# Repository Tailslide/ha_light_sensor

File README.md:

# Home Assistant Mouse Trap Monitor

An ESP32-based mouse trap monitoring system that integrates with Home Assistant via MQTT. The system uses light-dependent resistors (LDRs) to detect both the trap state (triggered/ready) and battery status (ok/low), providing real-time updates to your Home Assistant instance.

## Features

- Monitors mouse trap state (triggered/ready) using an LDR sensor
- Monitors battery status (ok/low) using a second LDR sensor
- Optional external wake circuit support for immediate trap detection
- Integrates with Home Assistant via MQTT
- Power-efficient design with deep sleep between readings
- 24-hour heartbeat publishing to ensure device health monitoring
- MQTT will messages for accurate availability tracking
- Configurable sampling parameters and thresholds
- Automatic state persistence across deep sleep cycles
- Robust WiFi and MQTT connection handling
- Modular code structure for better maintainability
- Configurable debug output

## Project Structure

The project follows a modular architecture for better organization and maintainability:

```
├── main/                  # Core application code
│   ├── include/          # Header files
│   │   ├── common.h     # Common definitions and utilities
│   │   ├── wifi_manager.h # WiFi connection management
│   │   ├── mqtt_manager.h # MQTT client operations
│   │   ├── sensor_manager.h # ADC and sensor handling
│   │   ├── led_controller.h # LED control functions
│   │   └── diagnostic.h  # Diagnostic mode operations
│   ├── src/             # Source files
│   │   ├── main.c      # Main application entry
│   │   ├── wifi_manager.c # WiFi implementation
│   │   ├── mqtt_manager.c # MQTT implementation
│   │   ├── sensor_manager.c # Sensor implementation
│   │   ├── led_controller.c # LED implementation
│   │   └── diagnostic.c # Diagnostic implementation
│   └── CMakeLists.txt   # Component build configuration
└── traps/               # Trap-specific configurations
    ├── backdoor/       # Back door trap config
    │   ├── config.h.template # Configuration template
    │   └── secrets.h.template # Credentials template
    ├── garage_near/    # Garage near trap config
    │   ├── config.h.template # Configuration template
    │   └── secrets.h.template # Credentials template
    └── template/       # Template for new traps
        ├── config.h.template # Configuration template
        └── secrets.h.template # Credentials template
```
## Hardware Requirements

- ESP32 development board ( M5Stamp C3)
- 2x Light Dependent Resistors (LDRs)
- Voltage divider resistors for LDRs
- Mouse trap with status LED and optional battery status LED (I use the OWL electronic mouse trap)

### Optional Wake Circuit Components
- TLV7011 comparator (or similar)
- GL5539 LDR (recommended for best sensitivity)
- 10kΩ resistor for LDR voltage divider
- 10kΩ trim potentiometer for threshold adjustment
- Connecting wires

## Pin Configuration

- GPIO4: LDR sensor for trap state detection (not needed if using wake circuit)
- GPIO1: LDR sensor for battery status detection
- GPIO2: Built-in RGB LED (using ESP32's led_strip driver)
- GPIO5: Wake circuit input (when USE_WAKE_CIRCUIT=1)

### Wake Circuit Connections
If using the optional wake circuit:
1. TLV7011 Pin 1 (OUT) → ESP32 GPIO5
2. TLV7011 Pin 2 (VEE) → GND
3. TLV7011 Pin 3 (IN+) → LDR voltage divider midpoint
4. TLV7011 Pin 4 (IN-) → Trim pot wiper (middle pin)
5. TLV7011 Pin 5 (VDD) → 3.3V

LDR Circuit:
```
3.3V ----[LDR]----+----[10kΩ]---- GND
                  |
                  +---- TLV7011 Pin 3 (IN+)
```

Trim Pot Circuit:
```
3.3V ----[10kΩ Trim Pot]----+---- GND
                            |
                            +---- TLV7011 Pin 4 (IN-)
```
- GPIO2: Built-in RGB LED (using ESP32's led_strip driver)

## Software Requirements

- ESP-IDF v5.x
- Home Assistant with MQTT broker

## Setup Instructions

The project now supports multiple mouse traps with individual configurations. Each trap has its own configuration directory under `traps/`.

### Available Traps
- `backdoor` - Back door mouse trap (original)
- `garage_near` - Garage near entrance trap
- Additional traps can be added by copying the `template` directory

### Power Optimization Settings

The project includes a `sdkconfig.defaults` file with optimized settings for power consumption:

```
# Power Management - Enable automatic power saving
CONFIG_PM_ENABLE=y
CONFIG_PM_DFS_INIT_AUTO=y
CONFIG_PM_USE_RTC_TIMER_REF=y

# CPU Frequency - Lower to 80MHz to save power
CONFIG_ESP_DEFAULT_CPU_FREQ_MHZ_80=y
CONFIG_ESP_DEFAULT_CPU_FREQ_MHZ=80

# Flash Power Down in Deep Sleep
CONFIG_ESP_SLEEP_POWER_DOWN_FLASH=y

# WiFi Power Saving
CONFIG_ESP_WIFI_SLP_IRAM_OPT=y
CONFIG_ESP_WIFI_SLP_DEFAULT_MIN_ACTIVE_TIME=100
CONFIG_ESP_WIFI_SLP_DEFAULT_MAX_ACTIVE_TIME=5
CONFIG_ESP_WIFI_STA_DISCONNECTED_PM_ENABLE=y

# Minimize Logging
CONFIG_LOG_DEFAULT_LEVEL_ERROR=y
CONFIG_LOG_DEFAULT_LEVEL=1
```

These settings are automatically applied during the build process and significantly reduce power consumption.

### Setting Up a New Trap

1. Clone this repository

2. Choose a trap to build:
   - Use existing traps in `traps/` directory
   - Or create a new trap by copying `traps/template`:
     ```
     copy traps\template traps\your_new_trap
     ```

3. Configure the trap:
   a. Copy `traps/your_trap/secrets.h.template` to `secrets.h` in the same directory:
      ```c
      #define WIFI_SSID "your_wifi_ssid"
      #define WIFI_PASS "your_wifi_password"
      #define MQTT_BROKER "your.mqtt.broker.ip"
      #define MQTT_USERNAME "your_mqtt_username"
      #define MQTT_PASSWORD "your_mqtt_password"
      ```
   b. Edit `traps/your_trap/config.h`:
      - Set TRAP_ID and TRAP_FRIENDLY_NAME
      - Adjust MQTT topics
      - Modify thresholds if needed
      - Configure other parameters as needed

4. Build and flash for a specific trap:
   ```bash
   # For backdoor trap (default if no trap specified)
   powershell -Command "& {. 'C:\Users\username\esp\v5.4\esp-idf\export.ps1'; idf.py build flash}"

   # For garage near trap (clean first when switching targets)
   powershell -Command "& {. 'C:\Users\username\esp\v5.4\esp-idf\export.ps1'; idf.py clean; idf.py -DTRAP_ID=garage_near build flash}"
   ```

   Note: Always run `idf.py clean` before building for a different trap target to ensure the correct configuration is used.

### Adding More Traps

1. Copy the template directory:
   ```
   copy traps\template traps\new_trap_name
   ```

2. Edit the new trap's config.h:
   - Update TRAP_ID (use underscores, e.g., garage_far)
   - Update TRAP_FRIENDLY_NAME
   - Update MQTT topics
   - Adjust thresholds based on location

3. Configure secrets.h as above

4. Build using:
   ```bash
   # Clean first when switching from another target
   powershell -Command "& {. 'C:\Users\username\esp\v5.4\esp-idf\export.ps1'; idf.py clean; idf.py -DTRAP_ID=new_trap_name build flash}"
   ```

## Configuration Parameters

### Debug Configuration
- `DEBUG_LOGS`: Set to 1 to enable debug messages, 0 to disable (default: 0)
  - When disabled, only essential system messages and diagnostic mode prompts are shown
  - When enabled, provides detailed operational status messages for debugging

### MQTT Configuration
- `MQTT_PORT`: MQTT broker port (default: 1883)
- `MQTT_TOPIC_CAUGHT`: Topic for trap state updates (default: "home/mousetrap/backdoor/state")
- `MQTT_TOPIC_BATTERY`: Topic for battery status updates (default: "home/mousetrap/backdoor/battery")
- `MQTT_TOPIC_AVAILABILITY`: Topic for device availability status (default: "home/mousetrap/backdoor/availability")

### Timing Configuration
- `BURST_DURATION_MS`: Duration of each sampling burst (default: 12000ms)
- `SAMPLE_INTERVAL_MS`: Interval between samples during burst (default: 20ms)
- `SLEEP_TIME_SECONDS`: Deep sleep duration between bursts (default: 30 minutes)
- `HEARTBEAT_INTERVAL_HOURS`: How often to force publish state updates (default: 24 hours)
- `CYCLES_PER_HOUR`: Automatically calculated based on sleep time (2 cycles per hour with default sleep time)
- `CYCLES_FOR_PUBLISH`: Automatically calculated based on HEARTBEAT_INTERVAL_HOURS and sleep time
  (e.g., with 30-minute sleep time and 24-hour interval: 2 cycles/hour * 24 hours = 48 cycles)

### Threshold Configuration
- `TRAP_THRESHOLD`: ADC threshold for trap triggered state (default: 50)
- `BATTERY_THRESHOLD`: ADC threshold for low battery state (default: 200)
- Note: These thresholds are calibrated for dark room conditions with the LDR pointed at a black surface. You may need to adjust based on your specific setup and ambient light conditions.

### Wake Circuit Configuration
- `USE_WAKE_CIRCUIT`: Set to 1 to enable external comparator wake circuit, 0 to use standard ADC sampling (default: 0)
- `WAKE_PIN`: GPIO pin connected to comparator output (default: GPIO5)
- Note: To test and calibrate the wake circuit, use diagnostic mode by holding the button during boot

## Home Assistant Configuration

Add configurations for each trap to your Home Assistant configuration. Here's the complete setup for both existing traps:

```yaml
mqtt:
  binary_sensor:
    # Back Door Trap
    - name: "Back Door Mouse Trap"
      unique_id: "backdoor_mousetrap_state"
      state_topic: "home/mousetrap/backdoor/state"
      payload_on: "triggered"
      payload_off: "ready"
      device_class: occupancy
      availability_topic: "home/mousetrap/backdoor/availability"
      payload_available: "online"
      payload_not_available: "offline"

    - name: "Back Door Mouse Trap Battery"
      unique_id: "backdoor_mousetrap_battery"
      state_topic: "home/mousetrap/backdoor/battery"
      payload_on: "low"
      payload_off: "ok"
      device_class: problem
      availability_topic: "home/mousetrap/backdoor/availability"
      payload_available: "online"
      payload_not_available: "offline"

    # Garage Near Trap
    - name: "Garage Near Mouse Trap"
      unique_id: "garage_near_mousetrap_state"
      state_topic: "home/mousetrap/garage_near/state"
      payload_on: "triggered"
      payload_off: "ready"
      device_class: occupancy
      availability_topic: "home/mousetrap/garage_near/availability"
      payload_available: "online"
      payload_not_available: "offline"

    - name: "Garage Near Mouse Trap Battery"
      unique_id: "garage_near_mousetrap_battery"
      state_topic: "home/mousetrap/garage_near/battery"
      payload_on: "low"
      payload_off: "ok"
      device_class: problem
      availability_topic: "home/mousetrap/garage_near/availability"
      payload_available: "online"
      payload_not_available: "offline"

# Template for additional traps (copy and modify for each new trap):
    # - name: "New Location Mouse Trap"
    #   unique_id: "new_location_mousetrap_state"
    #   state_topic: "home/mousetrap/new_location/state"
    #   payload_on: "triggered"
    #   payload_off: "ready"
    #   device_class: occupancy
    #   availability_topic: "home/mousetrap/new_location/availability"
    #   payload_available: "online"
    #   payload_not_available: "offline"
    #
    # - name: "New Location Mouse Trap Battery"
    #   unique_id: "new_location_mousetrap_battery"
    #   state_topic: "home/mousetrap/new_location/battery"
    #   payload_on: "low"
    #   payload_off: "ok"
    #   device_class: problem
    #   availability_topic: "home/mousetrap/new_location/availability"
    #   payload_available: "online"
    #   payload_not_available: "offline"
```

The MQTT will message feature ensures that sensors will automatically become `unavailable` if the device disconnects unexpectedly. This provides more accurate and immediate monitoring of device health compared to the previous `expire_after` approach.

Benefits of using MQTT will messages:
- Immediate notification when a device goes offline (no need to wait for a timeout)
- More accurate representation of device state
- Retained messages ensure the availability state persists even after Home Assistant restarts
- Reduces the "flapping" between unavailable and clear states when Home Assistant restarts

You can still create automations to monitor device health using the unavailable state:

```yaml
automation:
  - alias: "Back Door Mouse Trap Disconnected"
    trigger:
      - platform: state
        entity_id: binary_sensor.back_door_mouse_trap
        to: unavailable
    action:
      - service: notify.notify
        data:
          message: Your Back Door mouse trap hasn't reported in over 36 hours.

  - alias: "Garage Near Mouse Trap Disconnected"
    trigger:
      - platform: state
        entity_id: binary_sensor.garage_near_mouse_trap
        to: unavailable
    action:
      - service: notify.notify
        data:
          message: Your Garage Near mouse trap hasn't reported in over 36 hours.
```

These automations will notify you if any trap becomes unavailable, which happens automatically after 36 hours without updates (allowing a buffer over the 24-hour heartbeat).

## Operation

### Standard Operation (USE_WAKE_CIRCUIT=0)
1. The device wakes up every 30 minutes (configurable)
2. Performs burst sampling for 12 seconds to detect LED states
3. If any state has changed (trap triggered or battery low) or the configured heartbeat interval has elapsed:
    - Connects to WiFi
    - Connects to MQTT broker
    - Publishes "online" to the availability topic
    - Publishes the current state(s)
    - Resets the cycle counter
4. Goes back to deep sleep to conserve power

### Wake Circuit Operation (USE_WAKE_CIRCUIT=1)
1. The device configures two wake-up sources:
   - GPIO5 (connected to comparator output) - wakes immediately when trap is triggered
   - Timer - wakes every 30 minutes for battery check and heartbeat
2. When woken by GPIO5:
   - Immediately connects to WiFi/MQTT
   - Reports trap as triggered
   - Goes back to sleep
3. When woken by timer:
   - Samples only the battery sensor
   - Connects to WiFi/MQTT if battery state changed or heartbeat interval reached
   - Goes back to sleep

### Diagnostic Mode with Wake Circuit Support
When the device is started by holding down the button on boot, it enters diagnostic mode:
1. If wake circuit is enabled (USE_WAKE_CIRCUIT=1):
   - Continuously monitors the wake pin (GPIO5) for trap detection
   - Shows the RGB LED based on both wake pin and battery sensor states
   - Displays both wake pin state and LDR readings in the console
2. If wake circuit is not enabled:
   - Uses the standard LDR sensors for both trap and battery detection
   - Shows the RGB LED based on both sensor states

This mode allows for real-time adjustment of the trim pot to set the desired light threshold when using the wake circuit.

If the device disconnects unexpectedly, the MQTT broker will automatically publish the configured will message ("offline") to the availability topic, allowing Home Assistant to immediately mark the device as unavailable.

## Power Consumption

The device is designed to be power efficient:
- Uses deep sleep between readings
- Uses light sleep during burst sampling instead of active waiting
- Only connects to WiFi/MQTT when states change or every 24 hours
- WiFi power save mode (modem sleep) enabled during connections, reducing power consumption by ~60%
- Configurable sleep duration
- Minimal wake time with optimized sampling using sleep modes
- UART/Serial interface completely disabled after diagnostic mode check
- Serial output only enabled during initial boot and diagnostic mode
- GPIO pins for UART (TX/RX) reset to save power when not in use
- Power optimization settings in sdkconfig.defaults:
  - CPU frequency reduced to 80MHz
  - Flash powered down during deep sleep
  - WiFi power saving optimizations
  - Compiler optimized for size
  - Logging level minimized

The dual sleep mode strategy maximizes power efficiency:
1. Light sleep during burst sampling (20ms intervals)
   - Reduces power consumption during the 12-second sampling period
   - Maintains millisecond-level timing accuracy
   - CPU and most peripherals powered down between samples
2. Deep sleep between sampling cycles (30 minutes)
   - Maximum power savings during long idle periods
   - Only RTC and essential peripherals remain powered

## Troubleshooting

- If the sensor readings are inconsistent, adjust the `TRAP_THRESHOLD` and `BATTERY_THRESHOLD` values in `config.h`
- For more frequent updates, reduce `SLEEP_TIME_SECONDS`
- For more accurate readings, increase `BURST_DURATION_MS` or decrease `SAMPLE_INTERVAL_MS`
- For detailed operation logs, set `DEBUG_LOGS` to 1 in `config.h`
  - This will output detailed status messages for WiFi, MQTT, and sensor operations
  - Note: Critical system messages and diagnostic mode will always be shown regardless of this setting
- If the device is not waking properly from deep sleep:
  - Ensure the GPIO wake pin is properly configured with appropriate pull-up/pull-down resistors
  - For ESP32-C3, use `esp_deep_sleep_enable_gpio_wakeup()` instead of `gpio_wakeup_enable()` and `esp_sleep_enable_gpio_wakeup()`
  - Check for both `ESP_SLEEP_WAKEUP_GPIO` and `ESP_SLEEP_WAKEUP_EXT0` wake causes in your code
  - Properly configure the GPIO pin before enabling it as a wakeup source
  - Add a small delay before entering deep sleep to ensure all logs are printed
- If the wake circuit triggers but doesn't register as a trap event:
  - The latest firmware includes a fix for a race condition where brief wake pin triggers might not be detected
  - The system now considers a trap triggered if either:
    1. The current wake pin level is HIGH, or
    2. The device was woken by the wake circuit (even if the pin is now LOW)
  - This ensures that even momentary triggers will be properly detected and reported
  - The 2025-03-16 update includes additional debugging to ensure the wake circuit flag is properly set and maintained throughout the wake-up process
  - If you see inconsistent behavior with the wake circuit, update to the latest firmware version

### Power Optimization

- When using the wake circuit (USE_WAKE_CIRCUIT=1):
  - The device will only wake up when the trap is triggered or for the heartbeat interval
  - Sleep time is set to the HEARTBEAT_INTERVAL_HOURS (default 24 hours) instead of the 30-minute polling interval
  - This significantly reduces power consumption since the device doesn't need to wake up every 30 minutes
  - The wake circuit will immediately wake the device if the trap triggers, ensuring no events are missed
- Use the built-in diagnostic mode by holding the boot button during initial power-up (not available during wake from sleep):
  - The RGB LED will indicate sensor states in diagnostic mode:
    - Green: Mouse trap sensor triggered
    - Red: Battery sensor triggered
    - Yellow: Both sensors triggered
    - Blue: No sensors triggered
  - LED only activates in diagnostic mode to conserve power during normal operation
  - Diagnostic mode can only be entered during initial power-up, not during wake from sleep cycles
- For wake circuit troubleshooting:
  - Enter diagnostic mode by holding the button during boot
  - The diagnostic mode will automatically detect if wake circuit is enabled
  - Adjust the trim potentiometer until the LED turns green when the trap is triggered
  - The console will display both wake pin state and LDR readings
  - If the wake circuit is not working, check connections and verify the comparator is receiving power
  - Make sure the LDR is properly positioned to detect the trap's LED
  - In diagnostic mode with wake circuit enabled, the device will:
    - Show LED status based on both wake pin and battery sensor states
    - Not attempt to connect to WiFi or publish MQTT messages
    - Not enter sleep mode
    - Continuously monitor the wake pin state
- If WiFi connection fails during heartbeat:
  - The device will not reset its heartbeat counter and will try again on the next wake cycle
  - It will continue trying on each wake cycle until it successfully connects
  - No "offline" status is published until a successful connection is made and then lost
  - Home Assistant will continue to show the last known state until a successful update
  - WiFi issues won't affect the device's ability to monitor the trap - all states are preserved
- If you encounter build issues with macros in common.h, ensure there are no trailing backslashes at the end of lines
- If you see duplicate MQTT messages in the logs (e.g., "MQTT Connected" appearing twice), update to the latest version which fixes an issue with duplicate event handler registration in mqtt_manager.c

## License

This project is open source and available under the MIT License.

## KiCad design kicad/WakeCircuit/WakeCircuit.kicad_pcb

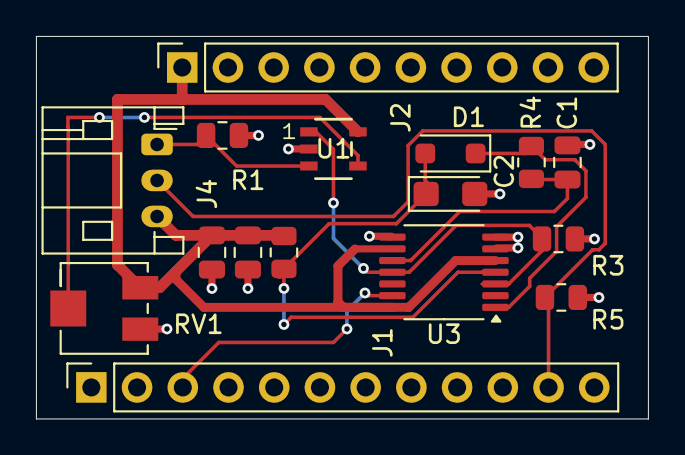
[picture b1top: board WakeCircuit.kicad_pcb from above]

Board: 2 copper layers, 34.0 x 21.2 mm, 16 parts (0 on the bottom side), 10 nets.

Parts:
C1, C3: 100nF; C_0805_2012Metric
C2: 22uF; CP_EIA-3216-18_Kemet-A
C4: 10uF; C_0805_2012Metric
D1: 1N4148; D_SOD-123F
J1: Conn_01x12_Socket; PinSocket_1x12_P2.54mm_Vertical
J2: Conn_01x10_Socket; PinSocket_1x10_P2.54mm_Vertical
J4: Conn_01x03_Socket; JST_PH_S3B-PH-K_1x03_P2.00mm_Horizontal
R1, R3, R4: 10K; R_0805_2012Metric
R2: 2.2M; R_0805_2012Metric
R5: 1.2K; R_0805_2012Metric
RV1: 10K; Potentiometer_Bourns_3214J_Horizontal
U1: TLV7011DBVR; SOT_1DBVR_TEX
U3: 4013; TSSOP-14_4.4x5mm_P0.65mm

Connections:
+3V3: C3.1, C4.2, J2.1, J4.3, R2.2, RV1.1, U1.5 (VCC), U3.5 (D), U3.9 (D), U3.14 (VDD)
GND: C1.2, C2.2, C3.2, C4.1, J1.1, J1.9, J2.6, J2.10, R1.1, R3.2, R5.2, RV1.3, U1.2 (VEE), U3.6 (S), U3.7 (VSS), U3.8 (S)
GPIO_1: J1.11, J4.2, R5.1
GPIO_5: J1.3, U3.13 (Q)
LDR_SIG: J4.1, R1.2, U1.3 (IN+)
unnamed: C2.1, D1.2 (A), R2.1, U3.4 (R)
unnamed: D1.1 (K), R4.2, U3.1 (Q)
unnamed: RV1.2, U1.4 (IN-)
unnamed: R3.1, U1.1 (OUT), U3.3 (C), U3.11 (C)
unnamed: C1.1, R4.1, U3.10 (R)

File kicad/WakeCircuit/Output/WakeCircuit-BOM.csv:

"Reference","Qty","Value","Description","DNP","Exclude from BOM","Exclude from Board","Footprint","Datasheet","PartNumber"
"C1,C3","2","100nF","Unpolarized capacitor","","","","Capacitor_SMD:C_0805_2012Metric","~","CC0805KKX7R0BB104 "
"C2","1","22uF","Polarized capacitor","","","","Capacitor_Tantalum_SMD:CP_EIA-3216-18_Kemet-A","~","TAJA226K010RNJ "
"C4","1","10uF","Unpolarized capacitor","","","","Capacitor_SMD:C_0805_2012Metric","~","CL21A106MPFNNNE"
"D1","1","1N4148","100V 0.15A standard switching diode, DO-35","","","","Diode_SMD:D_SOD-123F","https://assets.nexperia.com/documents/data-sheet/1N4148_1N4448.pdf","1N4148W-7-F "
"J1","1","Conn_01x12_Socket","Generic connector, single row, 01x12, script generated","","","","Connector_PinSocket_2.54mm:PinSocket_1x12_P2.54mm_Vertical","~","BCS-112-L-S-TE"
"J2","1","Conn_01x10_Socket","Generic connector, single row, 01x10, script generated","","","","Connector_PinSocket_2.54mm:PinSocket_1x10_P2.54mm_Vertical","~","BCS-110-L-S-TE"
"J4","1","Conn_01x03_Socket","Generic connector, single row, 01x03, script generated","","","","Connector_JST:JST_PH_S3B-PH-K_1x03_P2.00mm_Horizontal","~","S3B-PH-K(LF)(SN)"
"LDR1,LDR2","2","GL5539","light dependent resistor","","Excluded from BOM","Excluded from board","OptoDevice:R_LDR_4.9x4.2mm_P2.54mm_Vertical","https://docs.pedalpcb.com/datasheet/GL55.pdf",""
"R1,R3,R4","3","10K","Resistor","","","","Resistor_SMD:R_0805_2012Metric","~","RC0805FR-0710KL "
"R2","1","2.2M","Resistor","","","","Resistor_SMD:R_0805_2012Metric","~","RC0805FR-072M2L "
"R5","1","1.2K","Resistor","","","","Resistor_SMD:R_0805_2012Metric","~","RC0805FR-071K2L"
"RV1","1","10K","Trim-potentiometer","","","","Potentiometer_SMD:Potentiometer_Bourns_3214J_Horizontal","~","3214J-1-103E"
"U1","1","TLV7011DBVR","","","","","TLV7011DBVR:SOT_1DBVR_TEX","TLV7011DBVR","TLV7011DBVR"
"U3","1","4013","Dual D  FlipFlop, Set & reset","","","","Package_SO:TSSOP-14_4.4x5mm_P0.65mm","http://www.onsemi.com/pub/Collateral/MC14013B-D.PDF","CD4013BPW "

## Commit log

2025-01-18 Fixup makelists
2025-01-18 Add MQTT support (untested)
2025-01-24 Batter optimizations
2025-01-24 Improve network handling, update readme
2025-01-24 Add debugging
2025-01-24 Successfully updating queue
2025-01-24 Fix state updating every wake from sleep
2025-01-24 Add button press to put unit in sensor debug mode
2025-01-24 Code re-org
2025-01-24 Fix compiler warning
2025-01-24 Fix component references
2025-01-24 LED working
2025-01-24 Sensing mode lights up leds
2025-01-24 Wake from sleep optimizations
2025-01-24 Power saving optimizations
2025-01-24 Set LED to blue while sensing
2025-01-24 Add 24 hour heartbeat and home assistant example
2025-01-24 Disable serial port if not debugging to save power
2025-01-24 Enable wifi power saving mode
2025-01-24 Light sleep while sensing to save power
2025-01-24 Update threshold levels
2025-01-25 Calibrate sensors improve debugging
2025-01-25 Handle multiple traps
2025-01-25 Add template config examples for each trap
2025-01-25 Remove config from main folder
2025-01-29 Fix detection of unavailable
2025-02-02 Fix heartbeat not updating
2025-02-03 Fix heartbeat
2025-03-15 Add support for MQTT availability, wake circuit (untested)
2025-03-16 fix: Refactor wake circuit debug implementation
2025-03-16 feat: integrate wake circuit into diagnostic mode
2025-03-16 fix: improve deep sleep wake and MQTT stability
2025-03-16 fix: improve trap detection for momentary triggers
2025-03-16 feat: optimize power usage with wake circuit
2025-03-16 feat: Add power optimization settings & config file
2025-03-16 docs: add sdkconfig.orig to gitignore
2025-03-16 feat: update sleep config with wake circuit info
2025-03-28 Addd Latching Circuit
2025-04-08 PCB updates
2025-04-08 PCB Update
2025-04-09 Cleanup schematic
2025-04-09 Assigned footprints
2025-04-09 Update PCB
2025-04-10 PCB layout
2025-04-10 Update missing component 3d cad files
2025-04-11 V1 of PCB
2025-04-11 WakeCircuitV1 for real
2025-04-12 Update BOM with Part Numbers
2025-05-12 fix: update active layer in WakeCircuit project

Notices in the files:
README.md:
License:
This project is open source and available under the MIT License.
